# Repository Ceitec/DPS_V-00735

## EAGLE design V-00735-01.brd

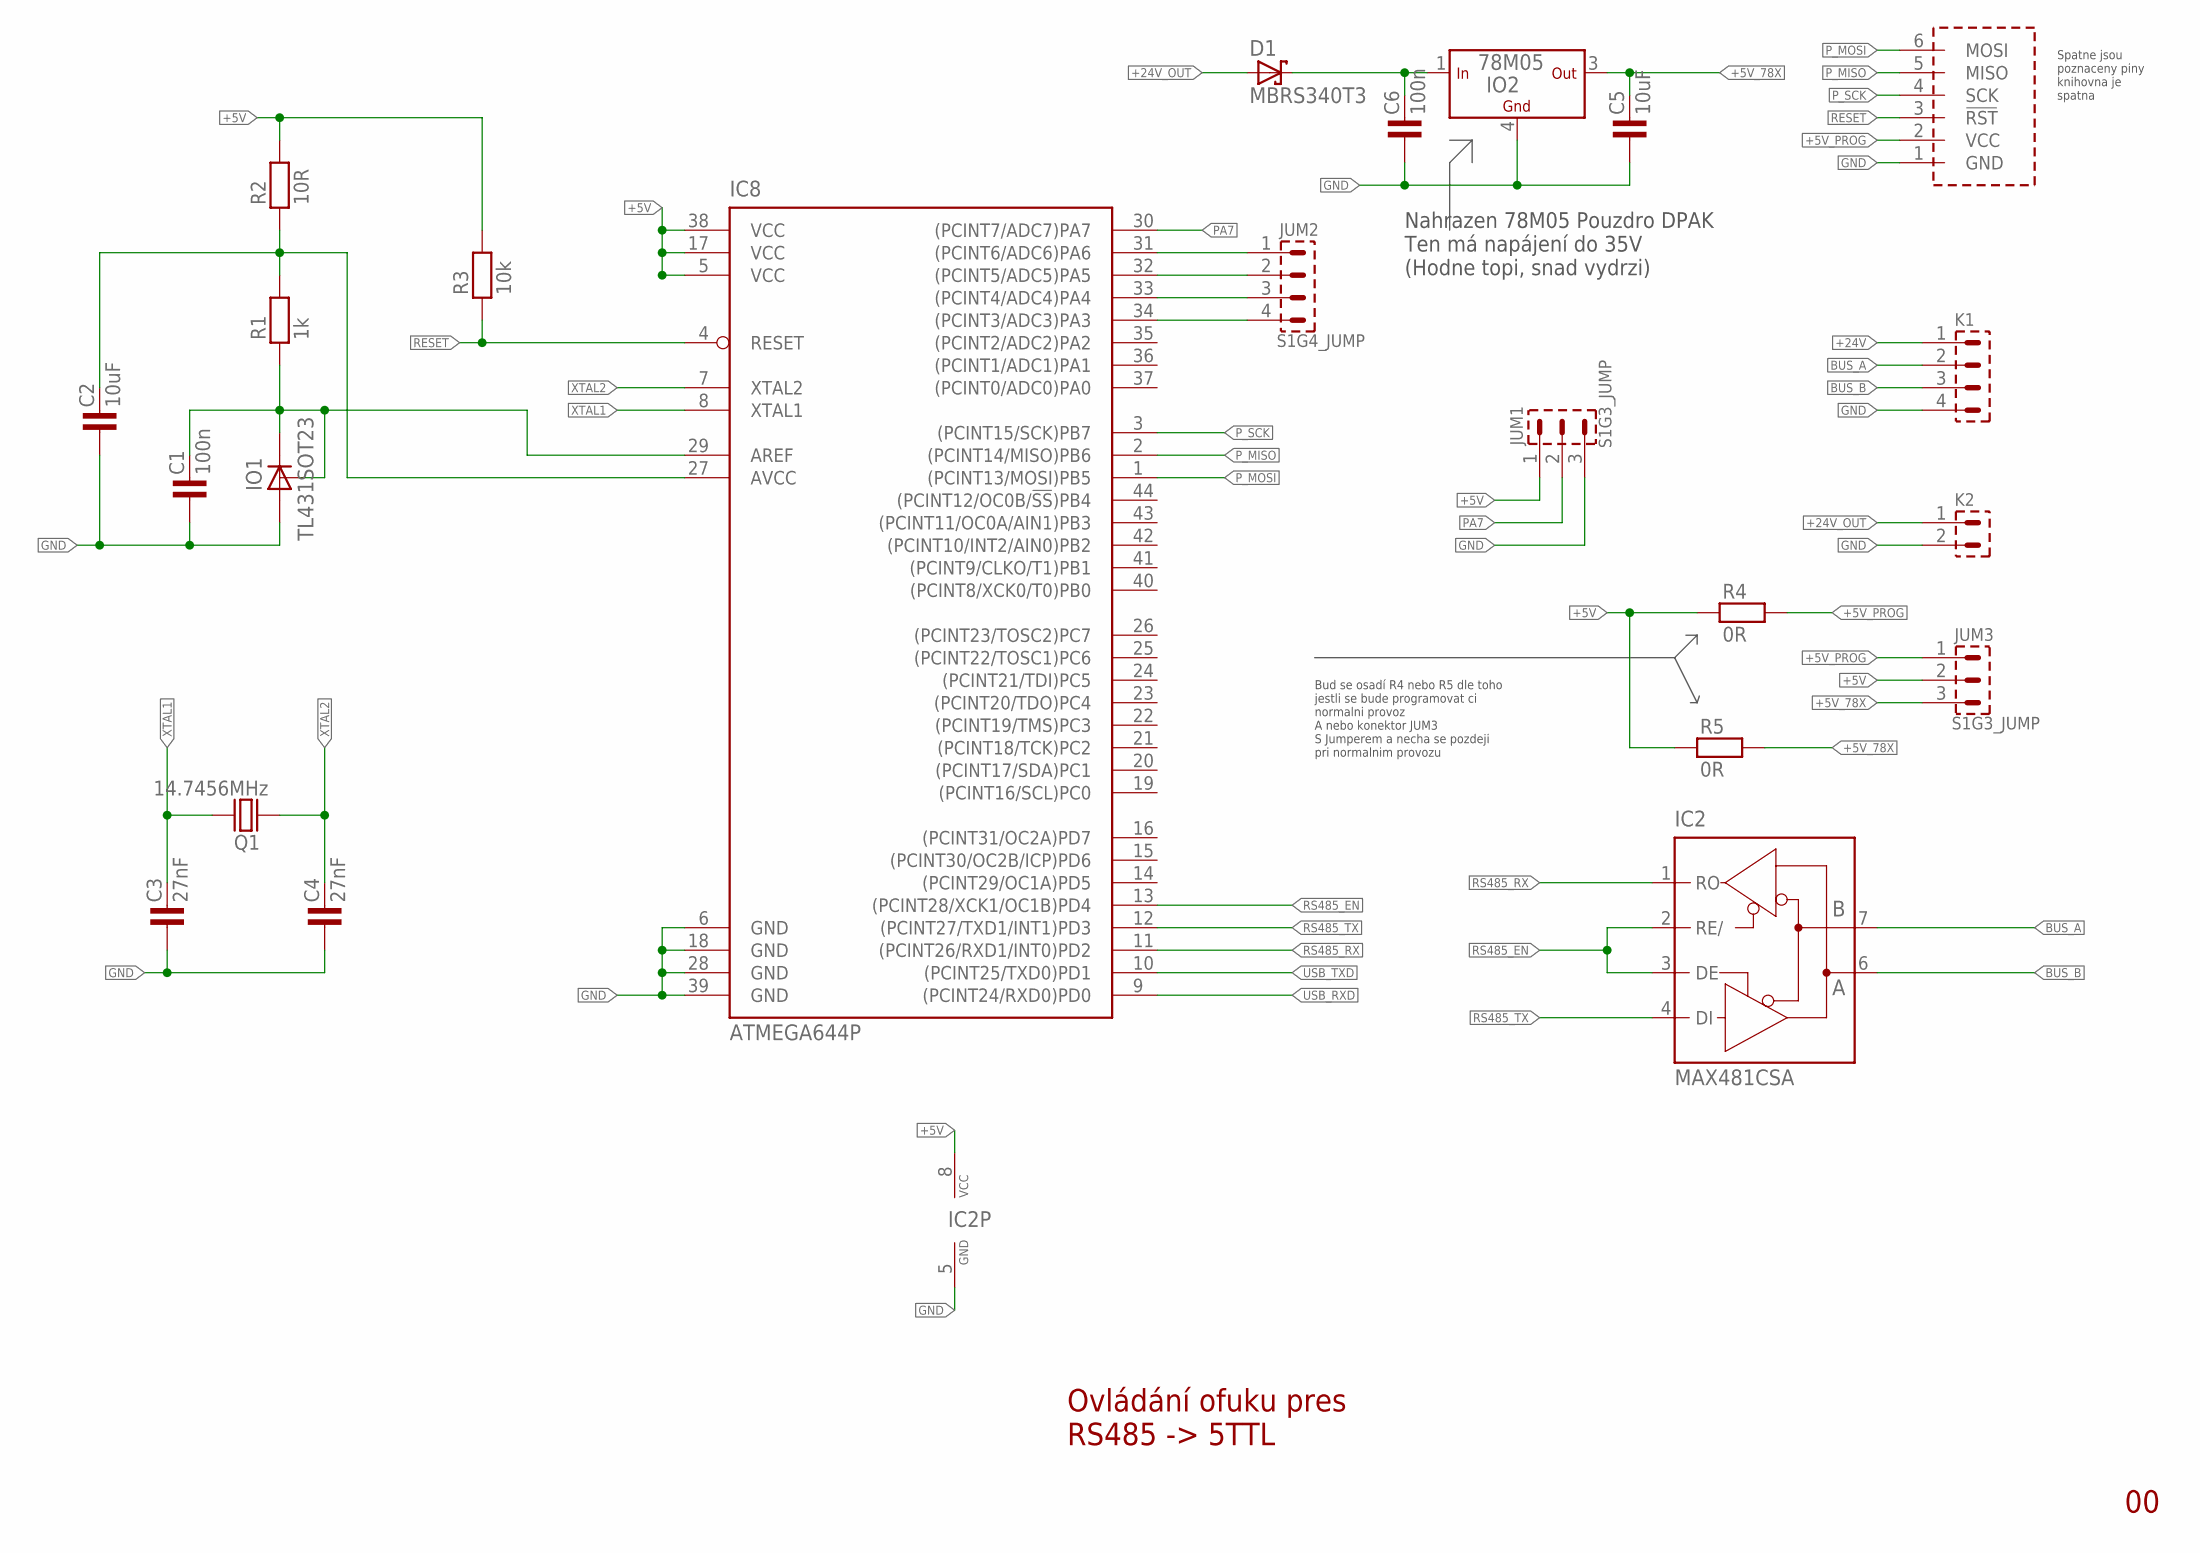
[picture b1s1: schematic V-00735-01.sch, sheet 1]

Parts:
C1, C6: 100n; 1206
C2, C5: 10uF; 1206
C3, C4: 27nF; 0805
D1: MBRS340T3; SMC
IC2: MAX481CSA; SO08
IC8: ATMEGA644P; TQFP44
IO1: TL431SOT23; SOT23
IO2: 78M05; DPAK
JUM1, JUM3: S1G3_JUMP; S1G3_JUM
JUM2: S1G4_JUMP; S1G4_JUM
K1: PSH02-04P
K2: PSH02-02P
Q1: 14.7456MHz; HC-49U
R1: 1k; 1206
R2: 10R; 1206
R3: 10k; 1206
R4, R5: 0R; 1206
U$1: AVR_PROG_SPI; PSH02-06P

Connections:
+5V: IC2.8 (VCC), IC8.5 (VCC), IC8.17 (VCC), IC8.38 (VCC), JUM1.1, JUM3.2, R2.2, R3.2, R4.1, R5.1; also elsewhere on the board
+5V_78X: C5.2, IO2.3 (OUT), JUM3.3, R5.2
+5V_PROG: JUM3.1, R4.2, U$1.2 (VCC)
+24V: C6.2, D1.C, IO2.1 (IN), K1.1
+24V_OUT: D1.A, K2.1
AREF: C1.2, IC8.29 (AREF), IO1.1 (C), IO1.2 (R), R1.1
AVCC: C2.2, IC8.27 (AVCC), R1.2, R2.1
BUS_A: IC2.7 (B), K1.2
BUS_B: IC2.6 (A), K1.3
GND: C1.1, C2.1, C3.1, C4.1, C5.1, C6.1, IC2.5 (GND), IC8.6 (GND), IC8.18 (GND), IC8.28 (GND), IC8.39 (GND), IO1.3 (A), IO2.4 (GND), JUM1.3, K1.4, K2.2, U$1.1 (GND); also elsewhere on the board
unnamed: IC8.31 ((PCINT6/ADC6)PA6), JUM2.1
unnamed: IC8.32 ((PCINT5/ADC5)PA5), JUM2.2
unnamed: IC8.33 ((PCINT4/ADC4)PA4), JUM2.3
unnamed: IC8.34 ((PCINT3/ADC3)PA3), JUM2.4
PA7: IC8.30 ((PCINT7/ADC7)PA7), JUM1.2
P_MISO: IC8.2 ((PCINT14/MISO)PB6), U$1.5 (MISO)
P_MOSI: IC8.1 ((PCINT13/MOSI)PB5), U$1.6 (MOSI)
P_SCK: IC8.3 ((PCINT15/SCK)PB7), U$1.4 (SCK)
RESET: IC8.4 (RESET), R3.1, U$1.3 (!RST)
RS485_EN: IC2.2 (RE/), IC2.3 (DE), IC8.13 ((PCINT28/XCK1/OC1B)PD4)
RS485_RX: IC2.1 (RO), IC8.11 ((PCINT26/RXD1/INT0)PD2)
RS485_TX: IC2.4 (DI), IC8.12 ((PCINT27/TXD1/INT1)PD3)
USB_RXD: IC8.9 ((PCINT24/RXD0)PD0); also elsewhere on the board
USB_TXD: IC8.10 ((PCINT25/TXD0)PD1); also elsewhere on the board
XTAL1: C3.2, IC8.8 (XTAL1), Q1.2
XTAL2: C4.2, IC8.7 (XTAL2), Q1.1

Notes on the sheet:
Ovládání ofuku pres RS485 -> 5TTL
Nahrazen 78M05 Pouzdro DPAK Ten má napájení do 35V (Hodne topi, snad vydrzi)
Spatne jsou poznaceny piny knihovna je spatna
Bud se osadí R4 nebo R5 dle toho jestli se bude programovat ci normalni provoz A nebo konektor JUM3 S Jumperem a necha se pozdeji pri normalnim provozu

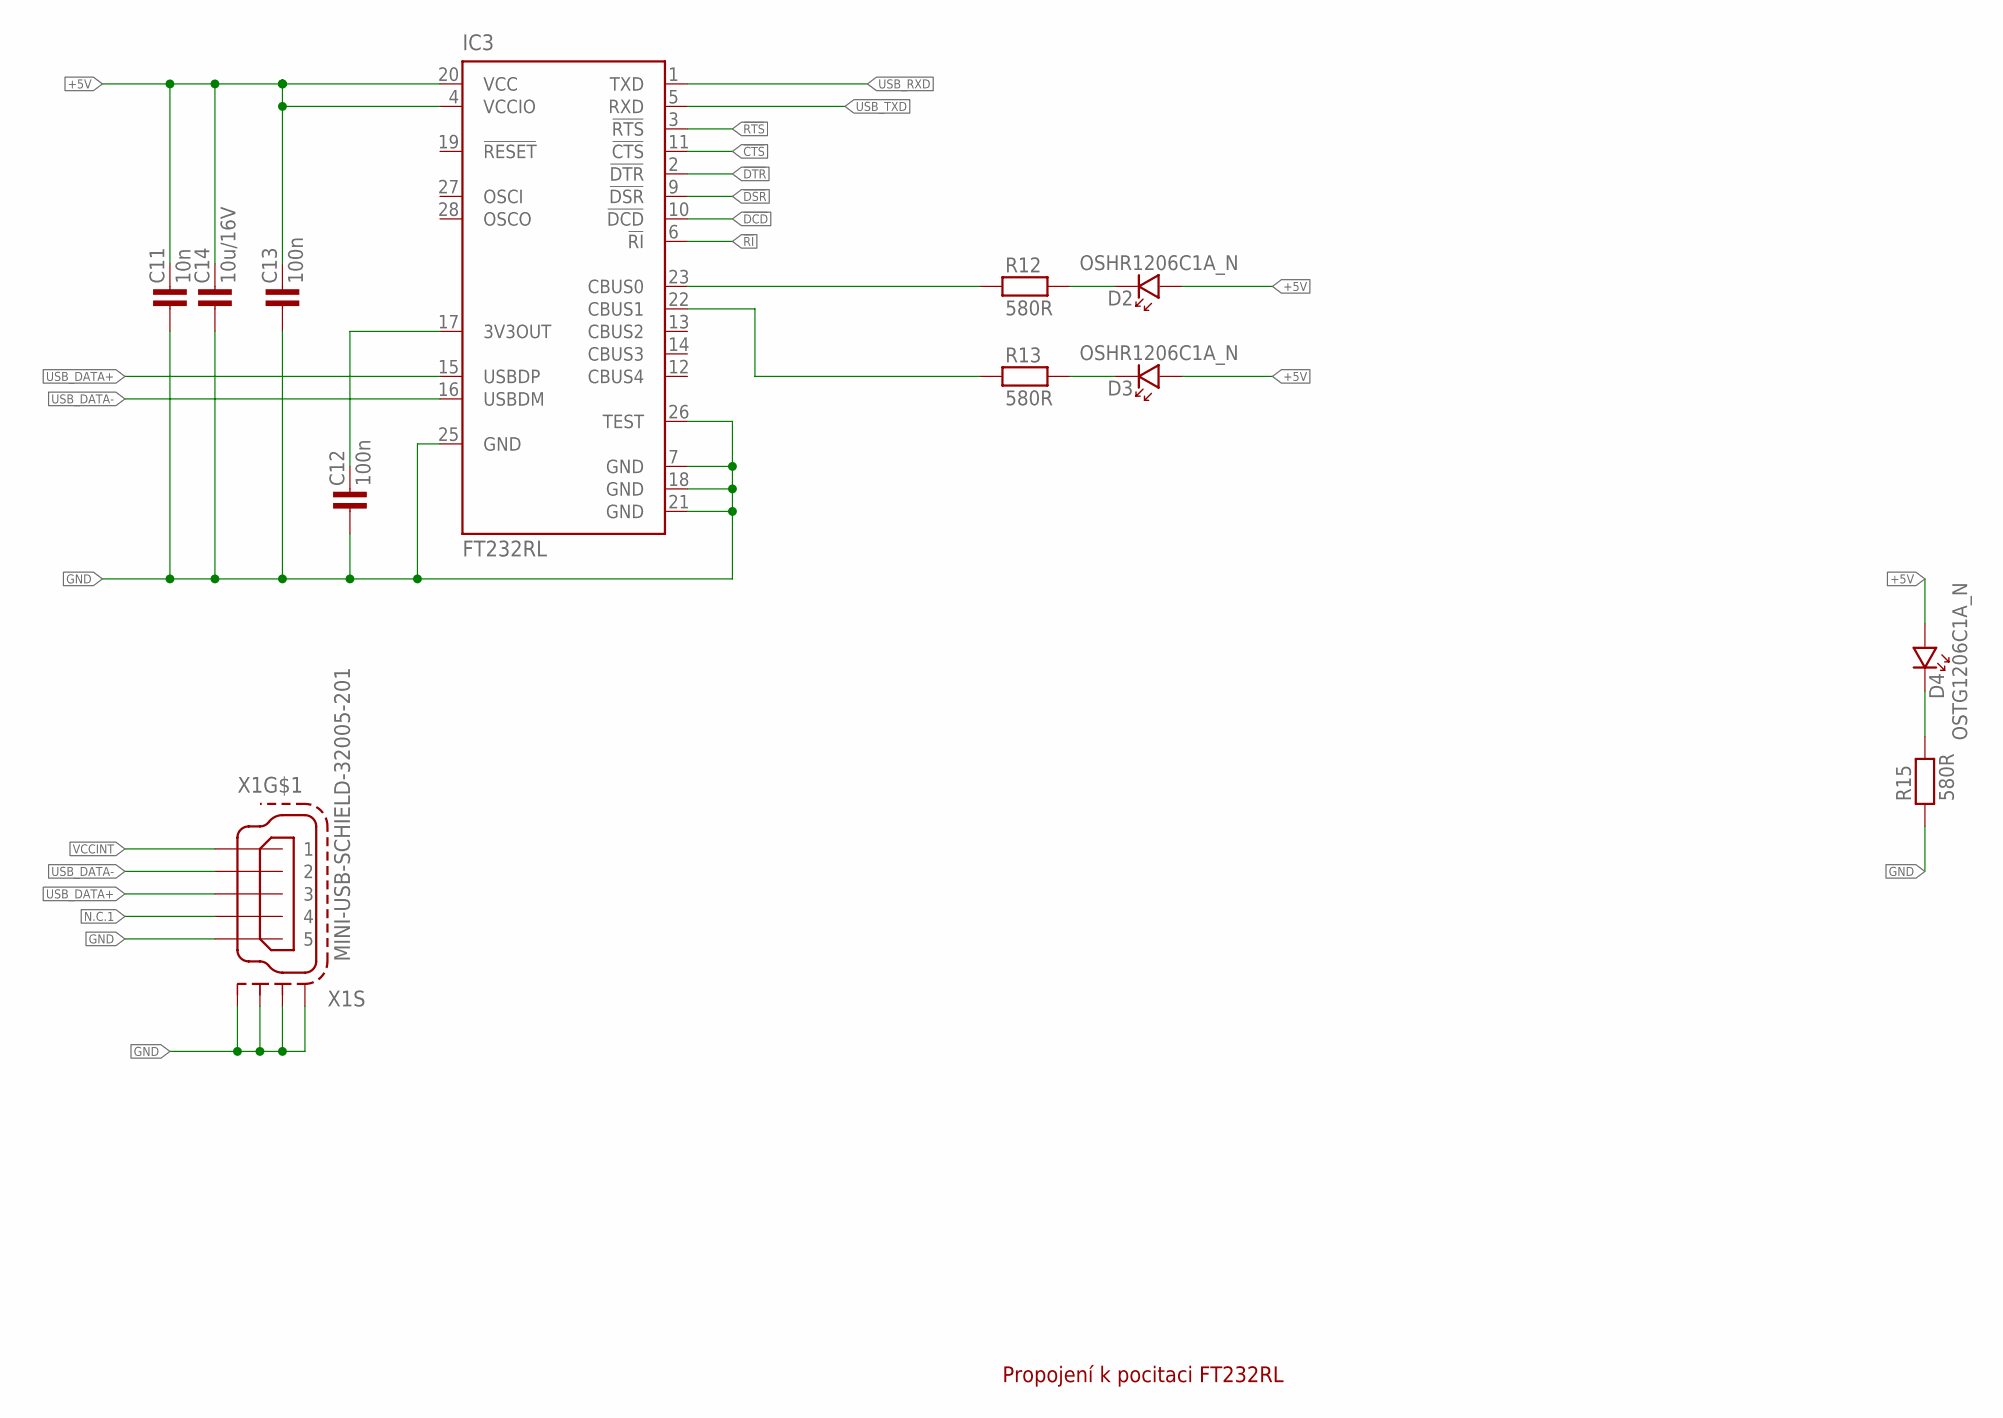
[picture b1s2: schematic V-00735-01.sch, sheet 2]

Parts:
C11: 10n; 1206
C12, C13: 100n; 1206
C14: 10u/16V; 1206
D2, D3: OSHR1206C1A_N; P1206
D4: OSTG1206C1A_N; P1206
IC3: FT232RL; SSOP28
R12, R13, R15: 580R; 1206
X1: MINI-USB-SCHIELD-32005-201; 32005-201

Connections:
!CTS: IC3.11 (!CTS)
!DCD: IC3.10 (!DCD)
!DSR: IC3.9 (!DSR)
!DTR: IC3.2 (!DTR)
!RI: IC3.6 (!RI)
!RTS: IC3.3 (!RTS)
+5V: C11.2, C13.2, C14.2, D2.A, D3.A, D4.A, IC3.4 (VCCIO), IC3.20 (VCC); also elsewhere on the board
GND: C11.1, C12.1, C13.1, C14.1, IC3.7 (GND), IC3.18 (GND), IC3.21 (GND), IC3.25 (GND), IC3.26 (TEST), R15.1, X1.5, X1.M1 (S1), X1.M2 (S2), X1.M3 (S3), X1.M4 (S4); also elsewhere on the board
unnamed: IC3.23 (CBUS0), R12.1
unnamed: IC3.22 (CBUS1), R13.1
unnamed: C12.2, IC3.17 (3V3OUT)
unnamed: D2.K, R12.2
unnamed: D3.K, R13.2
unnamed: D4.K, R15.2
N.C.1: X1.4
USB_DATA+: IC3.15 (USBDP), X1.3
USB_DATA-: IC3.16 (USBDM), X1.2
USB_RXD: IC3.1 (TXD); also elsewhere on the board
USB_TXD: IC3.5 (RXD); also elsewhere on the board
VCCINT: X1.1

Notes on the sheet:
Propojení k pocitaci FT232RL

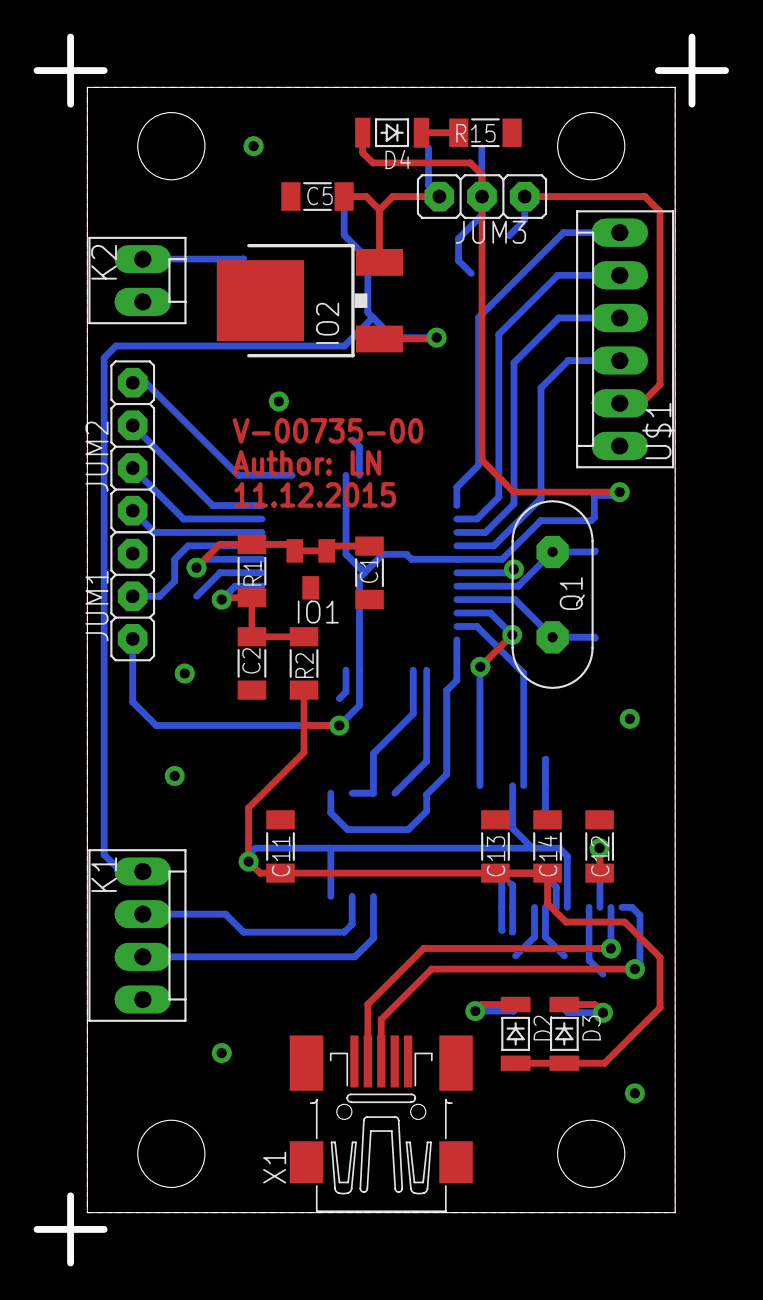
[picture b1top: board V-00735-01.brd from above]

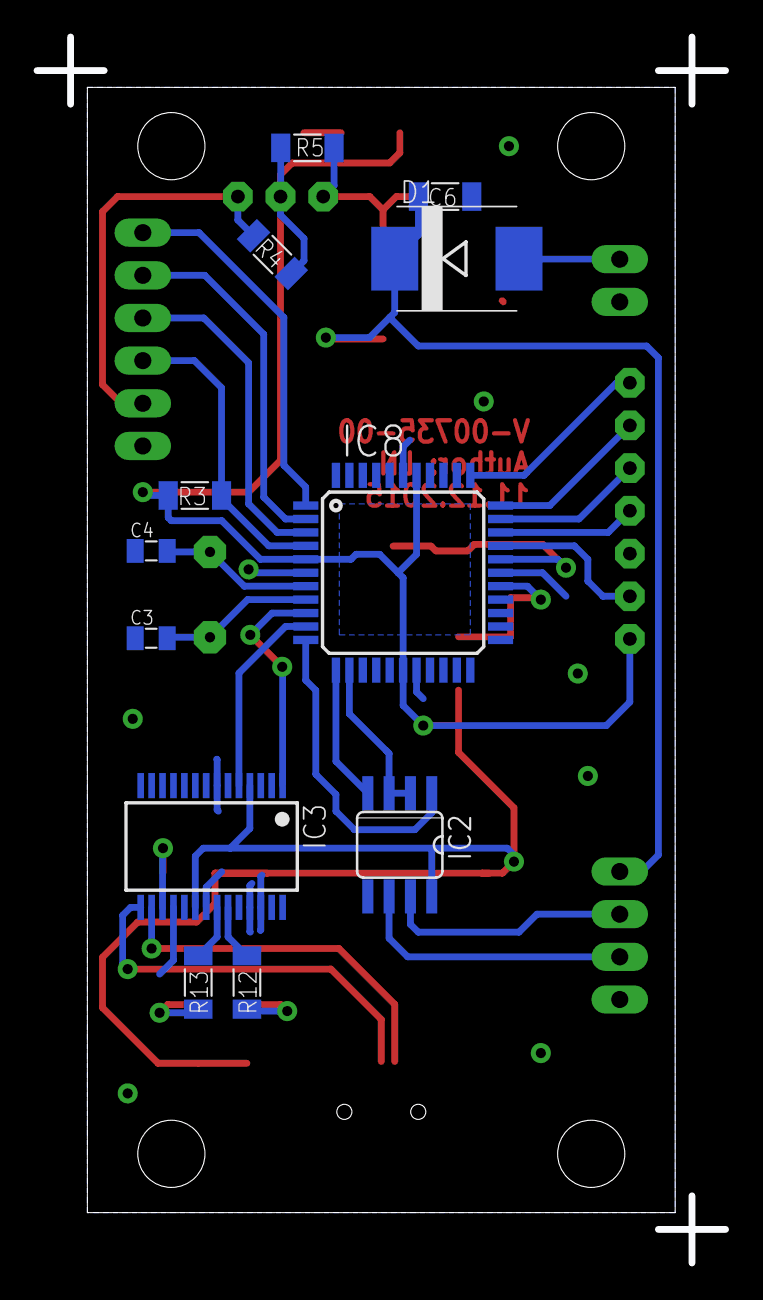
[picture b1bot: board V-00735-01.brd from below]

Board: 2 copper layers, 35.0 x 67.0 mm, 35 parts (12 on the bottom side), 34 nets.

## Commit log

2015-12-11 :lollipop: Added .gitattributes & .gitignore files
2015-12-11 v1.1.0.1
2015-12-29 v1.1.0.2
2015-12-29 v1.1.0.3
    Opraveny spoje, nevím proč ale byli divně pospojované. Ale plošnák OK.
    ALe nastal problém v stabilizátoru. Blbec jsem si nevšiml vstupního
    napájení které pro použitej stabilizátor je pouze 16V proto je nutné ho
    nahradit například 78L05-TO92
2016-02-10 v.2.0

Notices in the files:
parts and their libraries:
Copyright (C) PaJa 2001-2014
Copyright (C) PaJa 2011-2014
